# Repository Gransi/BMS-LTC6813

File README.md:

# BMS-LTC6813
BMS based on LTC6813-1 [PROTOTYPE]

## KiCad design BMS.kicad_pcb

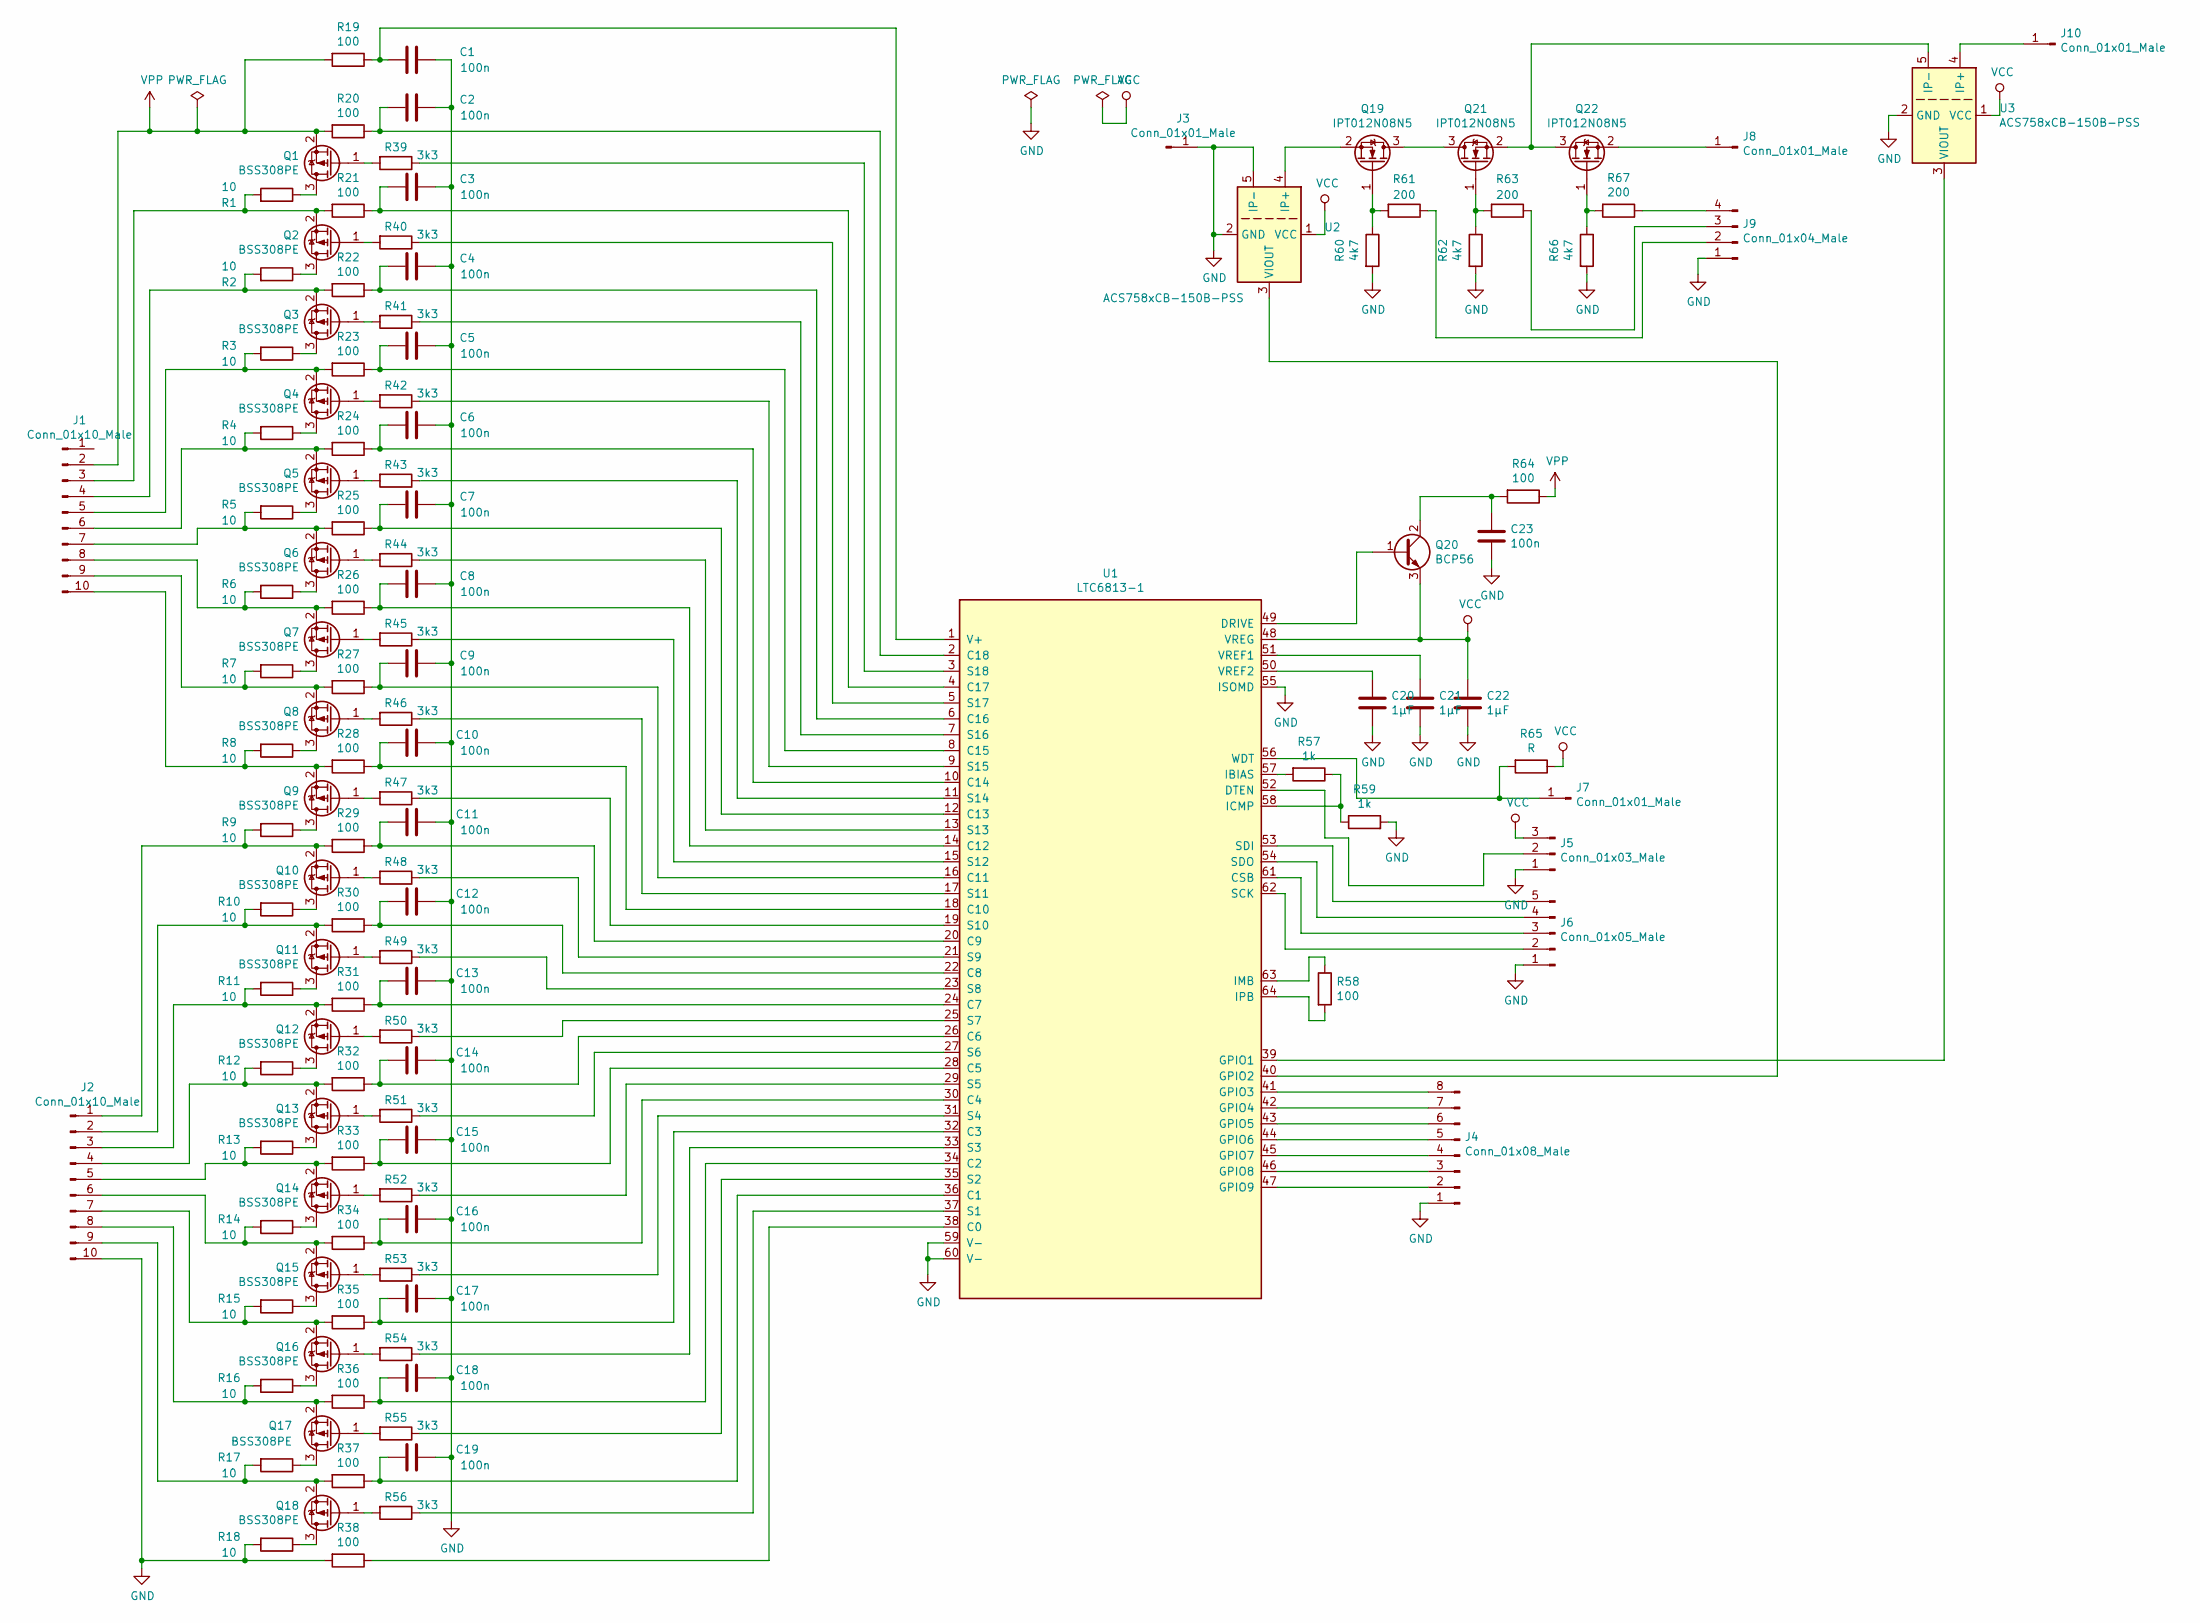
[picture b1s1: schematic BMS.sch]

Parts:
C1, C2, C3, C4, C5, C6, C7, C8, C9, C10, C11, C12, C13, C14, C15, C16, C17, C18, C19, C23: 100n; C_0805_2012Metric_Pad1.15x1.40mm_HandSolder
C20, C21, C22: 1µF; C_0805_2012Metric_Pad1.15x1.40mm_HandSolder
J1, J2: Conn_01x10_Male; PinHeader_1x10_P2.54mm_Vertical
J3, J8, J10: Conn_01x01_Male; TestPoint_Pad_4.0x4.0mm
J4: Conn_01x08_Male; PinHeader_1x08_P2.54mm_Vertical
J5: Conn_01x03_Male; PinHeader_1x03_P2.54mm_Vertical
J6: Conn_01x05_Male; PinHeader_1x05_P2.54mm_Vertical
J7: Conn_01x01_Male; PinHeader_1x01_P2.54mm_Vertical
J9: Conn_01x04_Male; PinHeader_1x04_P2.54mm_Vertical
Q1, Q2, Q3, Q4, Q5, Q6, Q7, Q8, Q9, Q10, Q11, Q12, Q13, Q14, Q15, Q16, Q17, Q18: BSS308PE; SOT-23
Q19, Q21, Q22: IPT012N08N5; Infineon_PG-HSOF-8-1
Q20: BCP56; SOT-223-3_TabPin2
R1, R2, R3, R4, R5, R6, R7, R8, R9, R10, R11, R12, R13, R14, R15, R16, R17, R18: 10; R_2512_6332Metric_Pad1.52x3.35mm_HandSolder
R19, R20, R21, R22, R23, R24, R25, R26, R27, R28, R29, R30, R31, R32, R33, R34, R35, R36, R37, R38: 100; R_1206_3216Metric_Pad1.42x1.75mm_HandSolder
R39, R40, R41, R42, R43, R44, R45, R46, R47, R48, R49, R50, R51, R52, R53, R54, R55, R56: 3k3; R_1206_3216Metric_Pad1.42x1.75mm_HandSolder
R57, R59: 1k; R_0805_2012Metric_Pad1.15x1.40mm_HandSolder
R58, R64: 100; R_0805_2012Metric_Pad1.15x1.40mm_HandSolder
R60, R62, R66: 4k7; R_0805_2012Metric_Pad1.15x1.40mm_HandSolder
R61, R63, R67: 200; R_0805_2012Metric_Pad1.15x1.40mm_HandSolder
R65: R; R_1206_3216Metric_Pad1.42x1.75mm_HandSolder
U1: LTC6813-1; LQFP-64-1EP_10x10mm_P0.5mm_EP6.5x6.5mm_ThermalVias
U2, U3: ACS758xCB-150B-PSS; Allegro_CB_PSS

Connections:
GND: C1.1, C2.1, C3.1, C4.1, C5.1, C6.1, C7.1, C8.1, C9.1, C10.1, C11.1, C12.1, C13.1, C14.1, C15.1, C16.1, C17.1, C18.1, C19.1, C20.2, C21.2, C22.2, C23.2, J2.10, J3.1, J4.1, J5.1, J6.1, J9.1, R18.2, R38.2, R59.2, R60.2, R62.2, R66.2, U1.55 (ISOMD), U1.59 (V-), U1.60 (V-), U2.2 (GND), U2.5 (IP-), U3.2 (GND)
unnamed: C1.2, R19.1, U1.1 (V+)
unnamed: C2.2, R20.1, U1.2 (C18)
unnamed: C3.2, R21.1, U1.4 (C17)
unnamed: C4.2, R22.1, U1.6 (C16)
unnamed: C5.2, R23.1, U1.8 (C15)
unnamed: C6.2, R24.1, U1.10 (C14)
unnamed: C7.2, R25.1, U1.12 (C13)
unnamed: C8.2, R26.1, U1.14 (C12)
unnamed: C9.2, R27.1, U1.16 (C11)
unnamed: C10.2, R28.1, U1.18 (C10)
unnamed: C11.2, R29.1, U1.20 (C9)
unnamed: C12.2, R30.1, U1.22 (C8)
unnamed: C13.2, R31.1, U1.24 (C7)
unnamed: C14.2, R32.1, U1.26 (C6)
unnamed: C15.2, R33.1, U1.28 (C5)
unnamed: C16.2, R34.1, U1.30 (C4)
unnamed: C17.2, R35.1, U1.32 (C3)
unnamed: C18.2, R36.1, U1.34 (C2)
unnamed: C19.2, R37.1, U1.36 (C1)
unnamed: C20.1, U1.50 (VREF2)
unnamed: C21.1, U1.51 (VREF1)
unnamed: C23.1, Q20.2 (C), Q20.4 (C), R64.2
unnamed: J1.3, Q2.2 (S), R1.2, R21.2
unnamed: J1.4, Q3.2 (S), R2.2, R22.2
unnamed: J1.5, Q4.2 (S), R3.2, R23.2
unnamed: J1.6, Q5.2 (S), R4.2, R24.2
unnamed: J1.7, Q6.2 (S), R5.2, R25.2
unnamed: J1.8, Q7.2 (S), R6.2, R26.2
unnamed: J1.9, Q8.2 (S), R7.2, R27.2
unnamed: J1.10, Q9.2 (S), R8.2, R28.2
unnamed: J2.1, Q10.2 (S), R9.2, R29.2
unnamed: J2.2, Q11.2 (S), R10.2, R30.2
unnamed: J2.3, Q12.2 (S), R11.2, R31.2
unnamed: J2.4, Q13.2 (S), R12.2, R32.2
unnamed: J2.5, Q14.2 (S), R13.2, R33.2
unnamed: J2.6, Q15.2 (S), R14.2, R34.2
unnamed: J2.7, Q16.2 (S), R15.2, R35.2
unnamed: J2.8, Q17.2 (S), R16.2, R36.2
unnamed: J2.9, Q18.2 (S), R17.2, R37.2
unnamed: J4.2, U1.47 (GPIO9)
unnamed: J4.3, U1.46 (GPIO8)
unnamed: J4.4, U1.45 (GPIO7)
unnamed: J4.5, U1.44 (GPIO6)
unnamed: J4.6, U1.43 (GPIO5)
unnamed: J4.7, U1.42 (GPIO4)
unnamed: J4.8, U1.41 (GPIO3)
unnamed: J5.2, U1.52 (DTEN)
unnamed: J6.2, U1.62 (SCK)
unnamed: J6.3, U1.61 (CSB)
unnamed: J6.4, U1.54 (SDO)
unnamed: J6.5, U1.53 (SDI)
unnamed: J7.1, R65.2, U1.56 (WDT)
unnamed: J8.1, Q22.2 (S)
unnamed: J9.2, R61.1
unnamed: J9.3, R63.1
unnamed: J9.4, R67.1
unnamed: J10.1, U3.4 (IP+)
unnamed: Q1.1 (G), R39.2
unnamed: Q1.3 (D), R1.1
unnamed: Q2.1 (G), R40.2
unnamed: Q2.3 (D), R2.1
unnamed: Q3.1 (G), R41.2
unnamed: Q3.3 (D), R3.1
unnamed: Q4.1 (G), R42.2
unnamed: Q4.3 (D), R4.1
unnamed: Q5.1 (G), R43.2
unnamed: Q5.3 (D), R5.1
unnamed: Q6.1 (G), R44.2
unnamed: Q6.3 (D), R6.1
unnamed: Q7.1 (G), R45.2
unnamed: Q7.3 (D), R7.1
unnamed: Q8.1 (G), R46.2
unnamed: Q8.3 (D), R8.1
unnamed: Q9.1 (G), R47.2
unnamed: Q9.3 (D), R9.1
unnamed: Q10.1 (G), R48.2
unnamed: Q10.3 (D), R10.1
unnamed: Q11.1 (G), R49.2
unnamed: Q11.3 (D), R11.1
unnamed: Q12.1 (G), R50.2
unnamed: Q12.3 (D), R12.1
unnamed: Q13.1 (G), R51.2
unnamed: Q13.3 (D), R13.1
unnamed: Q14.1 (G), R52.2
unnamed: Q14.3 (D), R14.1
unnamed: Q15.1 (G), R53.2
unnamed: Q15.3 (D), R15.1
unnamed: Q16.1 (G), R54.2
unnamed: Q16.3 (D), R16.1
unnamed: Q17.1 (G), R55.2
unnamed: Q17.3 (D), R17.1
unnamed: Q18.1 (G), R56.2
unnamed: Q18.3 (D), R18.1
unnamed: Q19.1 (G), R60.1, R61.2
unnamed: Q19.2 (S), U2.4 (IP+)
unnamed: Q19.3 (D), Q21.3 (D)
unnamed: Q20.1 (B), U1.49 (DRIVE)
unnamed: Q21.1 (G), R62.1, R63.2
unnamed: Q21.2 (S), Q22.3 (D), U3.5 (IP-)
unnamed: Q22.1 (G), R66.1, R67.2
unnamed: R38.1, U1.38 (C0)
unnamed: R39.1, U1.3 (S18)
unnamed: R40.1, U1.5 (S17)
unnamed: R41.1, U1.7 (S16)
unnamed: R42.1, U1.9 (S15)
unnamed: R43.1, U1.11 (S14)
unnamed: R44.1, U1.13 (S13)
unnamed: R45.1, U1.15 (S12)
unnamed: R46.1, U1.17 (S11)
unnamed: R47.1, U1.19 (S10)
unnamed: R48.1, U1.21 (S9)
unnamed: R49.1, U1.23 (S8)
unnamed: R50.1, U1.25 (S7)
unnamed: R51.1, U1.27 (S6)
unnamed: R52.1, U1.29 (S5)
unnamed: R53.1, U1.31 (S4)
unnamed: R54.1, U1.33 (S3)
unnamed: R55.1, U1.35 (S2)
unnamed: R56.1, U1.37 (S1)
unnamed: R57.1, R59.1, U1.58 (ICMP)
unnamed: R57.2, U1.57 (IBIAS)
unnamed: R58.1, U1.63 (IMB)
unnamed: R58.2, U1.64 (IPB)
unnamed: U1.39 (GPIO1), U3.3 (VIOUT)
unnamed: U1.40 (GPIO2), U2.3 (VIOUT)
VCC: C22.1, J5.3, Q20.3 (E), R65.1, U1.48 (VREG), U2.1 (VCC), U3.1 (VCC)
VPP: J1.2, Q1.2 (S), R19.2, R20.2, R64.1

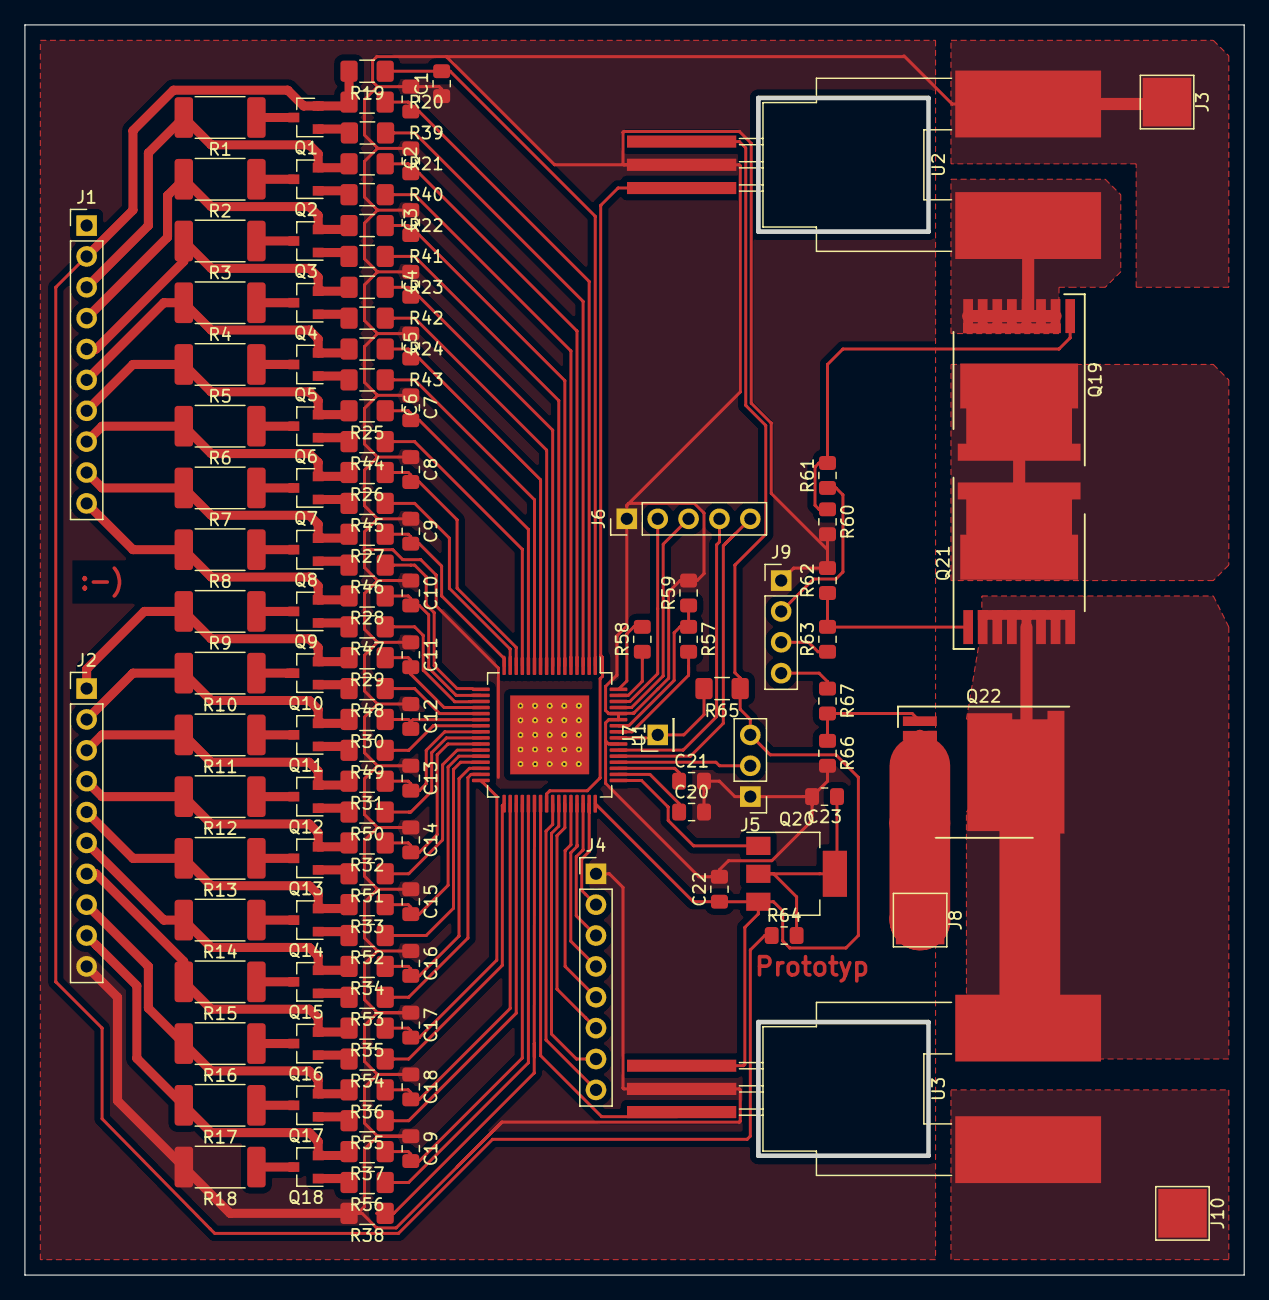
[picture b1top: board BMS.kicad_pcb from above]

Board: 2 copper layers, 100.0 x 102.6 mm, 125 parts (0 on the bottom side), 128 nets.

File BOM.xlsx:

Column1 | Column2 | Column3 | Column4 | Column5 | Column6 | Column7
Source: | C:\Users\Peter\Documents\BMS\BMS.sch
Date: | 24.03.2020 17:13:25
Tool: | Eeschema (5.1.5)-3
Generator: | C:\Program Files\KiCad\bin\scripting\plugins/bom_csv_grouped_by_value_with_fp.py
Component Count: | 125
Ref | Qnty | Value | Cmp name | Footprint | Description | Vendor
C1, C2, C3, C4, C5, C6, C7, C8, C9, C10, C11, C12, C13, C14, C15, C16, C17, C18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 | 20 | 100n | C | Capacitor_SMD:C_0805_2012Metric_Pad1.15x1.40mm_HandSolder | Unpolarized capacitor
C20, C21, C22, | 3 | 1ÂµF | C | Capacitor_SMD:C_0805_2012Metric_Pad1.15x1.40mm_HandSolder | Unpolarized capacitor
J1, J2, | 2 | Conn_01x10_Male | Conn_01x10_Male | Connector_PinHeader_2.54mm:PinHeader_1x10_P2.54mm_Vertical | Generic connector, single row, 01x10, script generated (kicad-library-utils/sch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
J3, J8, J10, | 3 | Conn_01x01_Male | Conn_01x01_Male | TestPoint:TestPoint_Pad_4.0x4.0mm | Generic connector, single row, 01x01, script generated (kicad-library-utils/sch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
J4, | 1 | Conn_01x08_Male | Conn_01x08_Male | Connector_PinHeader_2.54mm:PinHeader_1x08_P2.54mm_Vertical | Generic connector, single row, 01x08, script generated (kicad-library-utils/sch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
J5, | 1 | Conn_01x03_Male | Conn_01x03_Male | Connector_PinHeader_2.54mm:PinHeader_1x03_P2.54mm_Vertical | Generic connector, single row, 01x03, script generated (kicad-library-utils/sch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
J6, | 1 | Conn_01x05_Male | Conn_01x05_Male | Connector_PinHeader_2.54mm:PinHeader_1x05_P2.54mm_Vertical | Generic connector, single row, 01x05, script generated (kicad-library-utils/sch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
J7, | 1 | Conn_01x01_Male | Conn_01x01_Male | Connector_PinHeader_2.54mm:PinHeader_1x01_P2.54mm_Vertical | Generic connector, single row, 01x01, script generated (kicad-library-utils/sch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
J9, | 1 | Conn_01x04_Male | Conn_01x04_Male | Connector_PinHeader_2.54mm:PinHeader_1x04_P2.54mm_Vertical | Generic connector, single row, 01x04, script generated (kicad-library-utils/sch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
Q1, Q2, Q3, Q4, Q5, Q6, Q7, Q8, Q9, Q10, Q11, Q12, Q13, Q14, Q15, Q16, Q17, Q18, | 18 | BSS308PE | BSS83P | Package_TO_SOT_SMD:SOT-23 | -0.33A Id, -60V Vds, P-Channel MOSFET, SOT-23
Q19, Q21, Q22, | 3 | IPT012N08N5 | IPT012N08N5 | Package_TO_SOT_SMD:Infineon_PG-HSOF-8-1 | 300A Id, 80V Vds, OptiMOS N-Channel Power MOSFET, 1.2mOhm Ron, Qg (typ) 178.0nC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
Q20, | 1 | BCP56 | BCP56 | Package_TO_SOT_SMD:SOT-223-3_TabPin2 | 1A Ic, 80V Vce, NPN Medium Power Transistor, SOT-223
R1, R2, R3, R4, R5, R6, R7, R8, R9, R10, R11, R12, R13, R14, R15, R16, R17, R18, | 18 | 10 | R | Resistor_SMD:R_2512_6332Metric_Pad1.52x3.35mm_HandSolder | Resistor
R19, R20, R21, R22, R23, R24, R25, R26, R27, R28, R29, R30, R31, R32, R33, R34,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 | 20 | 100 | R | Resistor_SMD:R_1206_3216Metric_Pad1.42x1.75mm_HandSolder | Resistor
R39, R40, R41, R42, R43, R44, R45, R46, R47, R48, R49, R50, R51, R52, R53, R54,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 | 18 | 3k3 | R | Resistor_SMD:R_1206_3216Metric_Pad1.42x1.75mm_HandSolder | Resistor
R57, R59, | 2 | 1k | R | Resistor_SMD:R_0805_2012Metric_Pad1.15x1.40mm_HandSolder | Resistor
R58, R64, | 2 | 100 | R | Resistor_SMD:R_0805_2012Metric_Pad1.15x1.40mm_HandSolder | Resistor
R60, R62, R66, | 3 | 4k7 | R | Resistor_SMD:R_0805_2012Metric_Pad1.15x1.40mm_HandSolder | Resistor
R61, R63, R67, | 3 | 200 | R | Resistor_SMD:R_0805_2012Metric_Pad1.15x1.40mm_HandSolder | Resistor
R65, | 1 | R | R | Resistor_SMD:R_1206_3216Metric_Pad1.42x1.75mm_HandSolder | Resistor
U1, | 1 | LTC6813-1 | LTC6813-1-LTC6813-1 | Package_QFP:LQFP-64-1EP_10x10mm_P0.5mm_EP6.5x6.5mm_ThermalVias
U2, U3, | 2 | ACS758xCB-150B-PSS | ACS758xCB-150B-PSS | Sensor_Current:Allegro_CB_PSS | Â±150A Bidirectional Hall-Effect Current Sensor, +5.0V supply, 13.3mV/A, CB-5 P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

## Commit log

2020-03-06 first version
2020-03-07 Remove diode on charge input
2020-03-08 backup
2020-03-09 First routing
2020-03-24 First Version (Ordered)
2020-03-24 Add Excel BOM
